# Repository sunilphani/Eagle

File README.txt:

Versioning Note:

version 1.0: First Prototype. PCBs are done and some are soldered.
		1.0b: un-autorouted version

version 1.1: Small improvements to be considered in the next version.
			 PERFORM ALL YOUR CHANGES IN THIS VERSION OR OTHER SUBVERSIONS, NOT IN 1.0 SO AS TO KEEP THE ORIGINAL WAY IT WAS FABRICATED.

			 Changes made in this verision:
			 - added Filter Capacitors at weight sensor amplifier.

		1.1b: un-autorouted verison

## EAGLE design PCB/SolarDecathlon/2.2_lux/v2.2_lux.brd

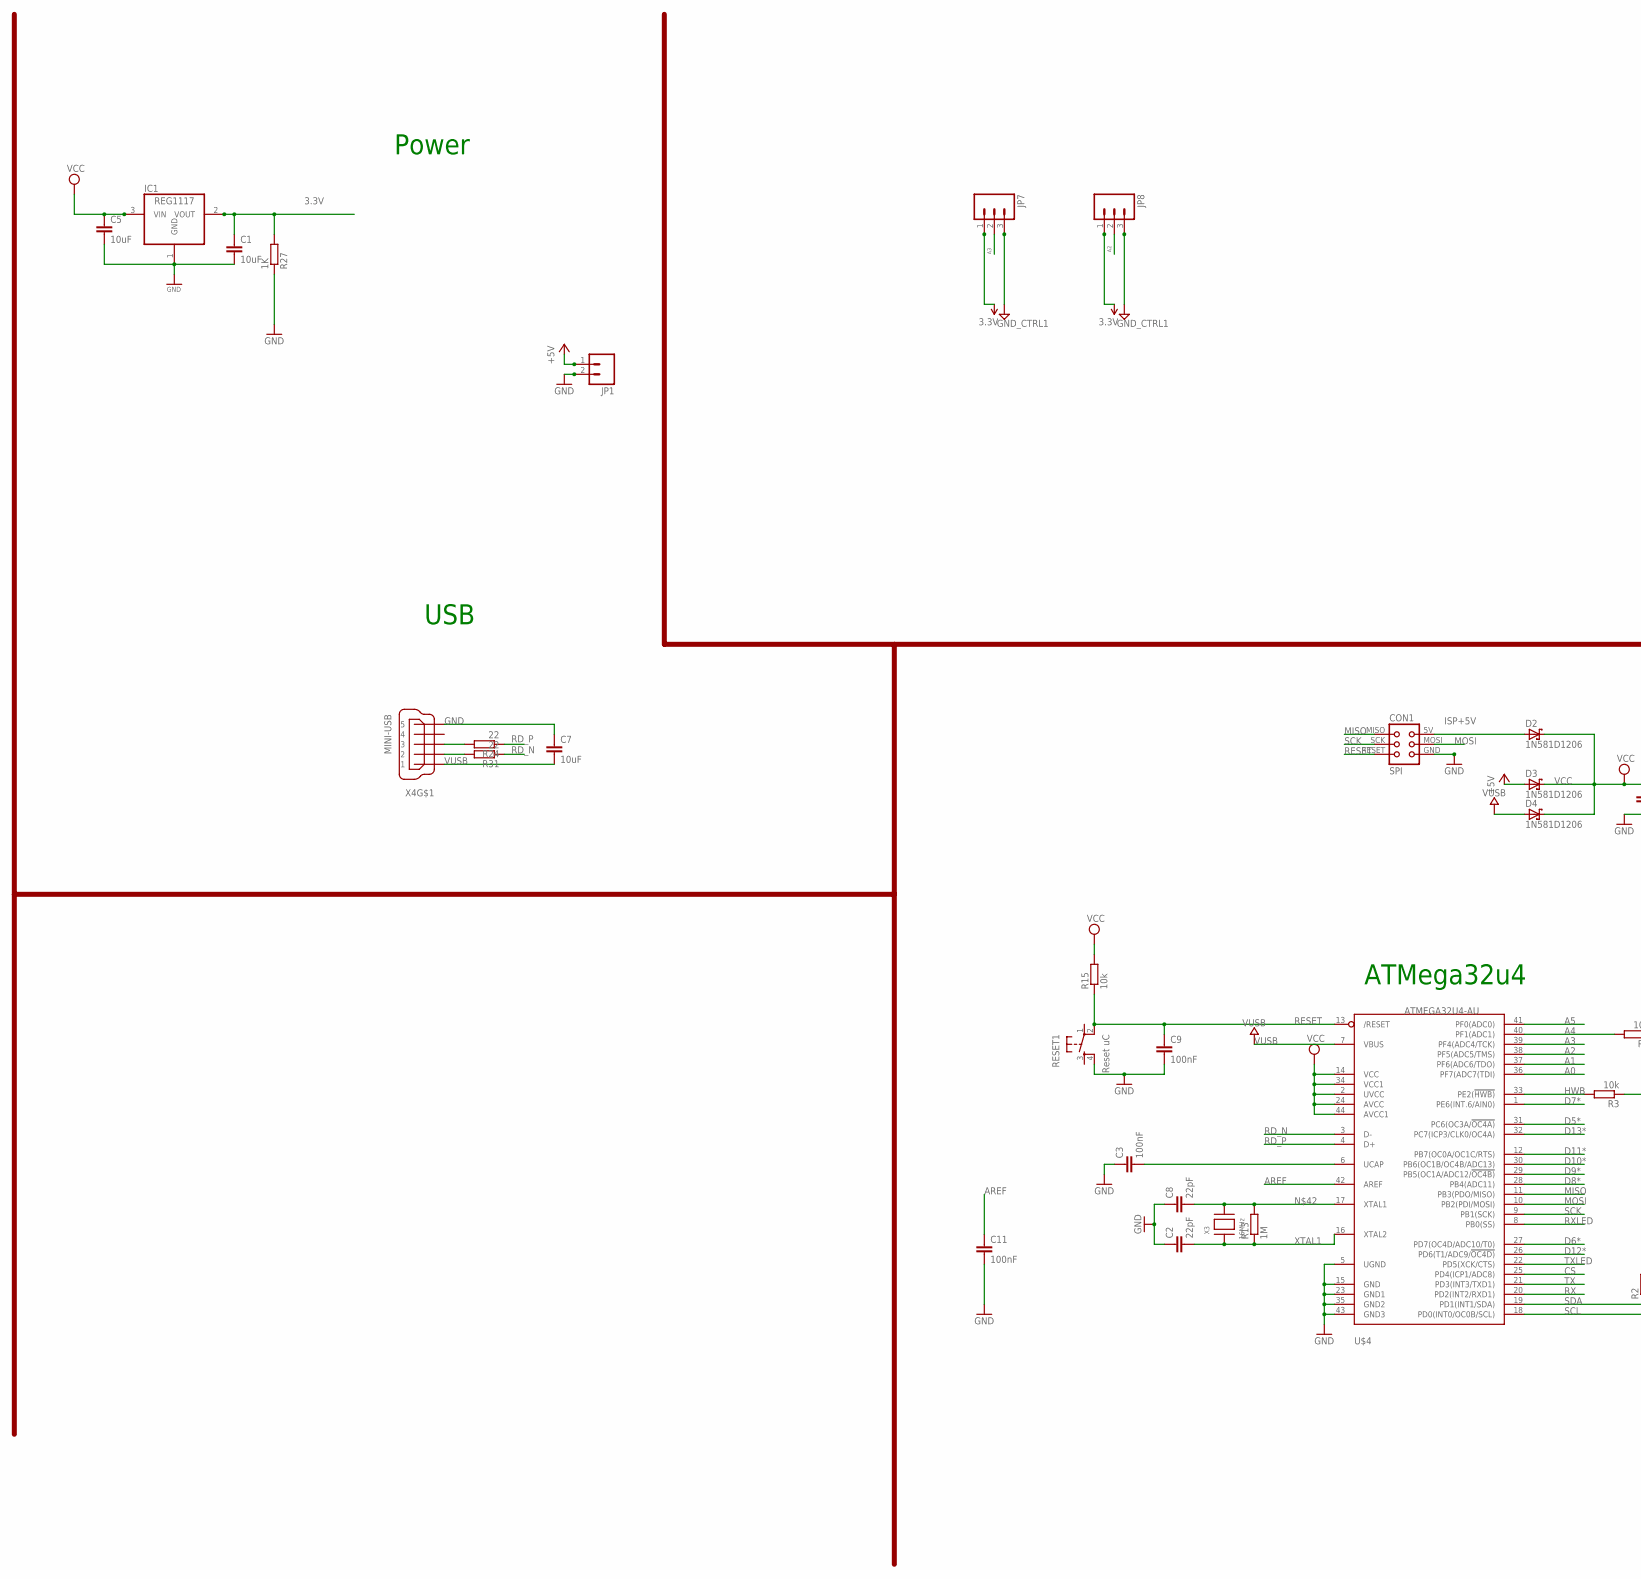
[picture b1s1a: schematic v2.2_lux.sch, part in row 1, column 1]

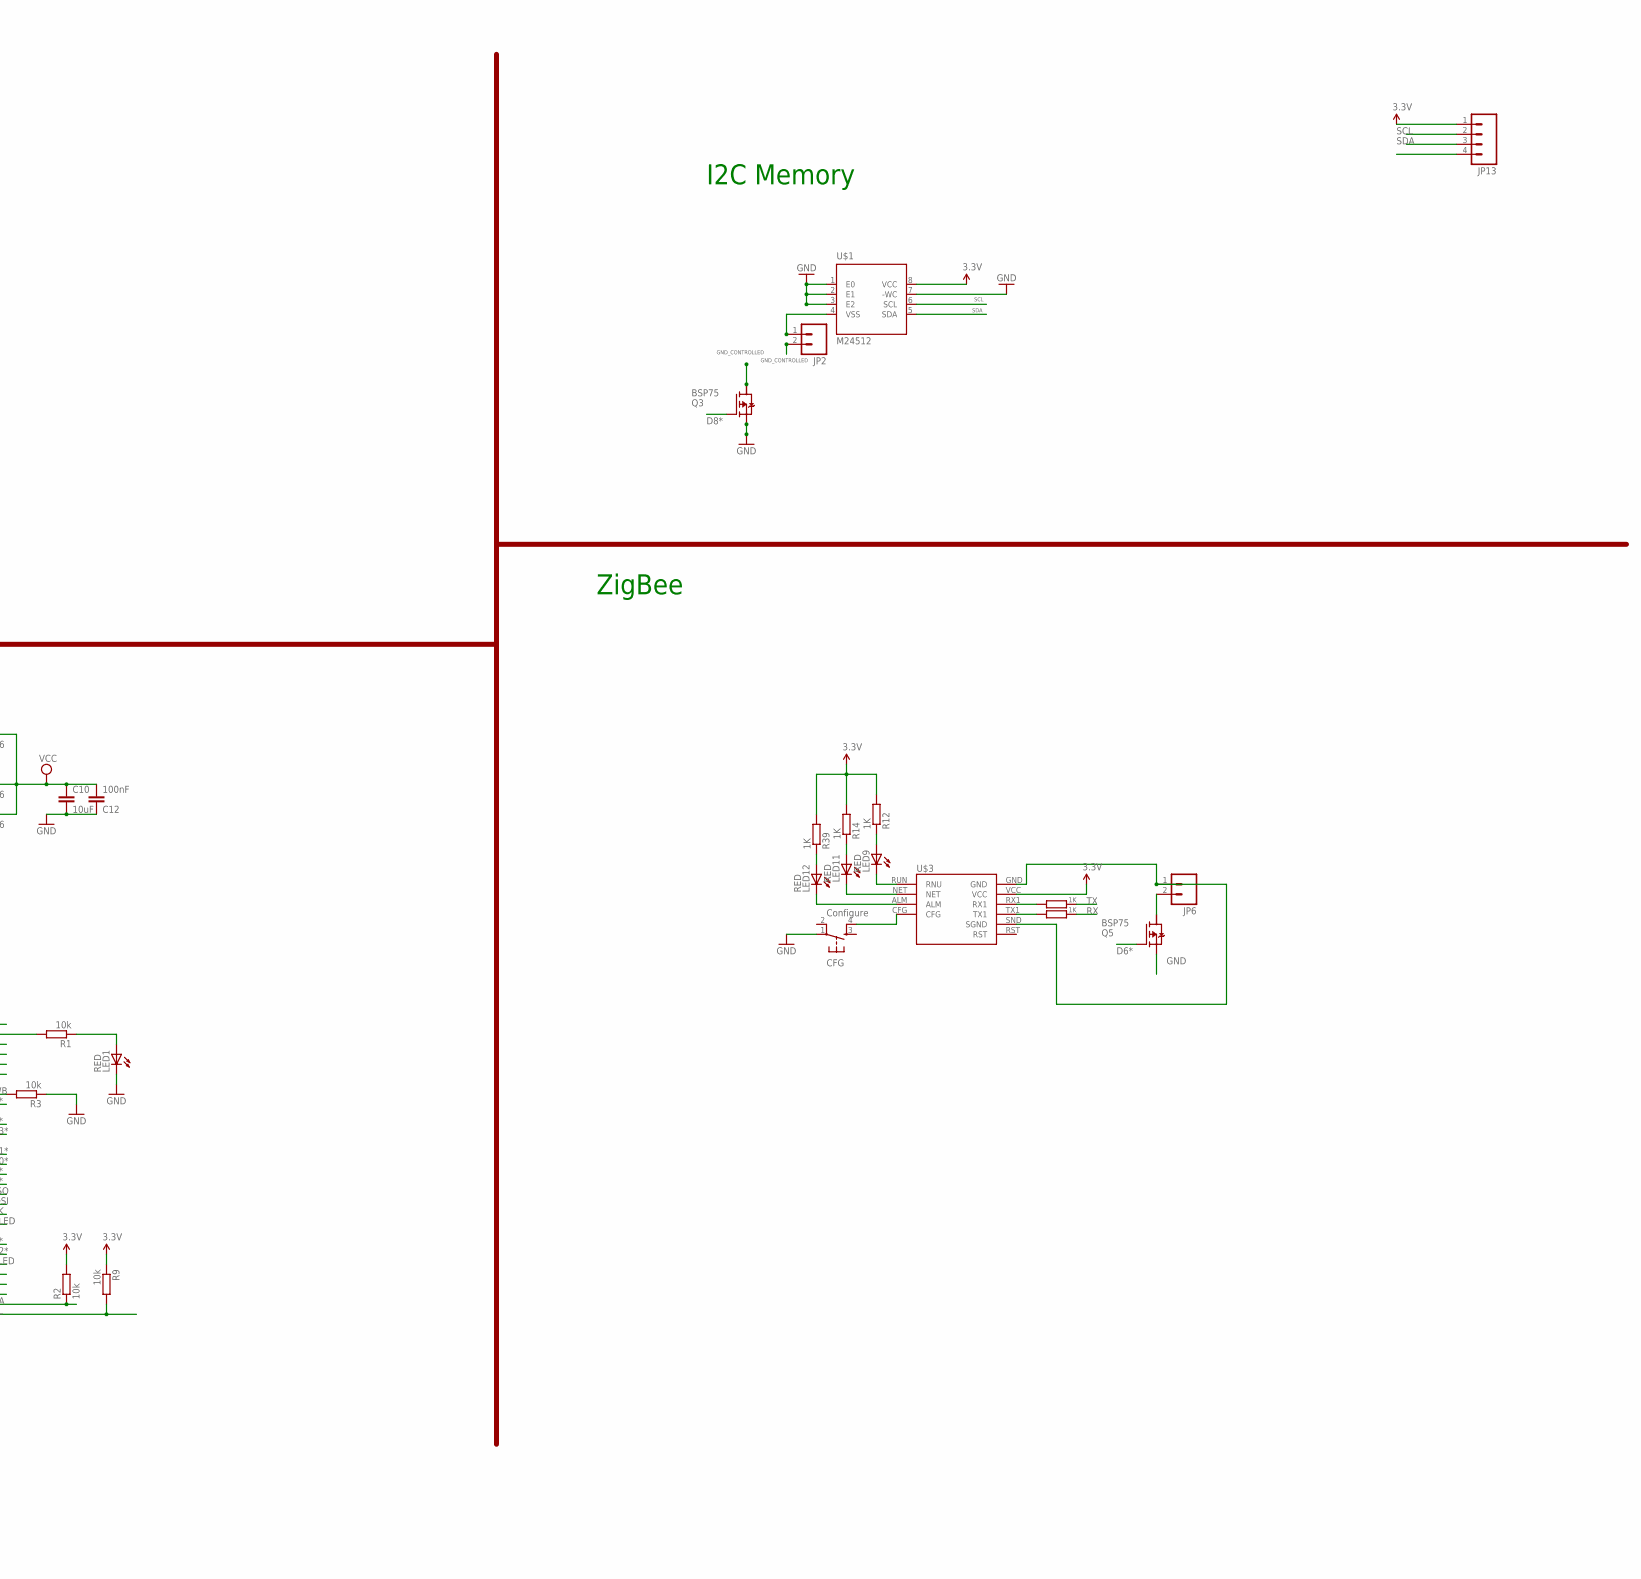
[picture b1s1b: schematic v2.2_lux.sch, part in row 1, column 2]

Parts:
C1, C5, C7, C10: 10uF; C1206
C2, C8: 22pF; C1206
C3, C9, C11, C12: 100nF; C1206
CFG: Configure; TACTILE_SWITCH_SMD
CON1: SPI; TC2030-MCP-NL
D2, D3, D4: 1N581D1206; LED-1206
IC1: REG1117; SOT223
JP1, JP2, JP6: M02LOCK_LONGPADS; 1X02_LOCK_LONGPADS
JP7, JP8: M03LONGPADS; 1X03_LONGPADS
JP13: M04LOCK_LONGPADS; 1X04_LOCK_LONGPADS
LED1, LED9, LED11, LED12: RED; CHIP-LED0805
Q3, Q5: BSP75; PG-SOT-223
R1, R2, R3, R9: 10k; M1206
R8, R11, R12, R14, R27, R39: 1K; R0805
R13: 1M; R1206
R15: 10k; M0805
R24, R31: 22; M1206
RESET1: Reset uC; TACTILE_SWITCH_SMD
U$1: M24512; SO8
U$3: SZ05-ZIGBEETHROUGHHOLE; SZ05-ZIGBEE4
U$4: ATMEGA32U4-AU; TQFP44
X3: 16MHz; NX6035
X4: MINI-USB; 32005-201

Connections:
3.3V: C1.1, IC1.2 (VOUT), JP7.1, JP8.1, JP13.1, R2.2, R9.1, R12.2, R14.2, R27.2, R39.2, U$1.8 (VCC), U$3.VCC
$12: JP2.1, U$1.4 (VSS)
+5V: D3.A, JP1.1
A0: U$4.36 (PF7(ADC7(TDI))
A1: U$4.37 (PF6(ADC6/TDO))
A2: JP8.2, U$4.38 (PF5(ADC5/TMS))
A3: JP7.2, U$4.39 (PF4(ADC4/TCK))
A4: R1.2, U$4.40 (PF1(ADC1))
A5: U$4.41 (PF0(ADC0))
AREF: C11.1, U$4.42 (AREF)
CS: U$4.25 (PD4(ICP1/ADC8))
D5*: U$4.31 (PC6(OC3A/!OC4A))
D6*: Q5.1 (G), U$4.27 (PD7(OC4D/ADC10/T0))
D7*: U$4.1 (PE6(INT.6/AIN0))
D8*: Q3.1 (G), U$4.28 (PB4(ADC11))
D9*: U$4.29 (PB5(OC1A/ADC12/!OC4B))
D10*: U$4.30 (PB6(OC1B/OC4B/ADC13))
D11*: U$4.12 (PB7(OC0A/OC1C/RTS))
D12*: U$4.26 (PD6(T1/ADC9/!OC4D))
D13*: U$4.32 (PC7(ICP3/CLK0/OC4A))
D+USB: R24.2, X4.3
D-USB: R31.2, X4.2
GND: C1.2, C2.1, C3.1, C5.2, C7.1, C8.1, C9.2, C10.2, C11.2, C12.1, CFG.1, CON1.GND, IC1.1 (GND), JP1.2, JP7.3, JP8.3, LED1.C, Q3.3 (S), Q5.3 (S), R3.1, R27.1, RESET1.4, U$1.1 (E0), U$1.2 (E1), U$1.3 (E2), U$1.7 (-WC), U$4.5 (UGND), U$4.15 (GND), U$4.23 (GND1), U$4.35 (GND2), U$4.43 (GND3), X4.5
GND1: LED9.C, U$3.RUN (RNU)
GND2: LED11.C, U$3.NET
GND3: LED12.C, U$3.ALM
GND_CONTROLLED: JP2.2, JP13.4, Q3.2 (D)
HWB: R3.2, U$4.33 (PE2(!HWB))
ISP+5V: CON1.5V (VCC), D2.A
MISO: CON1.MISO, U$4.11 (PB3(PDO/MISO))
MOSI: CON1.MOSI, U$4.10 (PB2(PDI/MOSI))
unnamed: LED1.A, R1.1
unnamed: JP6.2, Q5.2 (D)
unnamed: JP6.1, U$3.GND, U$3.SND (SGND)
unnamed: R11.2, U$3.RX1
unnamed: C3.2, U$4.6 (UCAP)
unnamed: R8.2, U$3.TX1
unnamed: LED9.A, R12.1
unnamed: LED11.A, R14.1
unnamed: LED12.A, R39.1
unnamed: CFG.4, U$3.CFG
unnamed: C8.2, R13.2, U$4.17 (XTAL1), X3.P$2
RD_N: R31.1, U$4.3 (D-)
RD_P: R24.1, U$4.4 (D+)
RESET: C9.1, CON1.RESET, R15.1, RESET1.2, U$4.13 (/RESET)
RX: R8.1, U$4.20 (PD2(INT2/RXD1))
RXLED: U$4.8 (PB0(SS))
SCK: CON1.SCK, U$4.9 (PB1(SCK))
SCL: JP13.2, R9.2, U$1.6 (SCL), U$4.18 (PD0(INT0/OC0B/SCL))
SDA: JP13.3, R2.1, U$1.5 (SDA), U$4.19 (PD1(INT1/SDA))
TX: R11.1, U$4.21 (PD3(INT3/TXD1))
TXLED: U$4.22 (PD5(XCK/CTS))
VCC: C5.1, C10.1, C12.2, D2.C, D3.C, D4.C, IC1.3 (VIN), R15.2, U$4.2 (UVCC), U$4.14 (VCC), U$4.24 (AVCC), U$4.34 (VCC1), U$4.44 (AVCC1)
VUSB: C7.2, D4.A, U$4.7 (VBUS), X4.1
XTAL1: C2.2, R13.1, U$4.16 (XTAL2), X3.P$1

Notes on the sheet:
I2C Memory
ATMega32u4
USB
Power
ZigBee

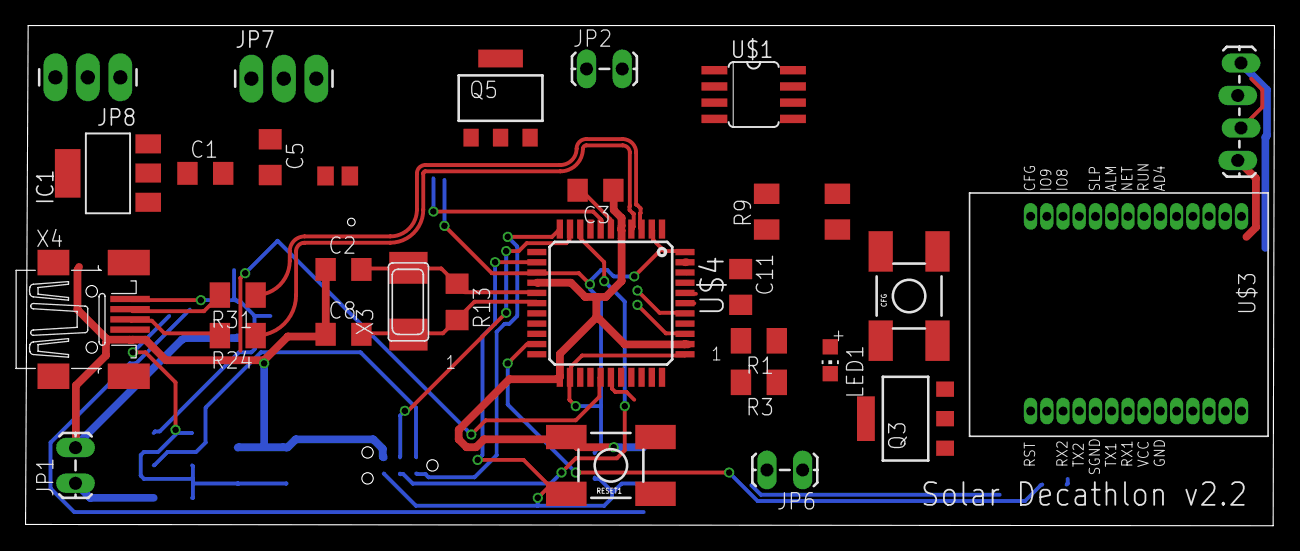
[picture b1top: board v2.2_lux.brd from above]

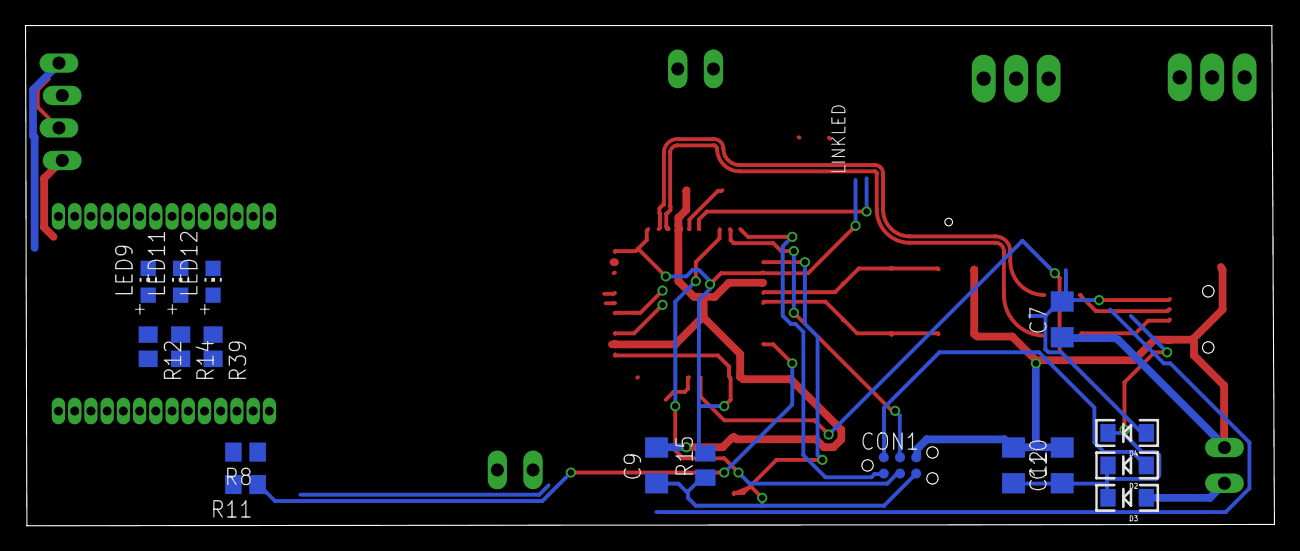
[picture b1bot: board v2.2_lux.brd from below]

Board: 2 copper layers, 97.8 x 39.2 mm, 48 parts (17 on the bottom side), 42 nets.

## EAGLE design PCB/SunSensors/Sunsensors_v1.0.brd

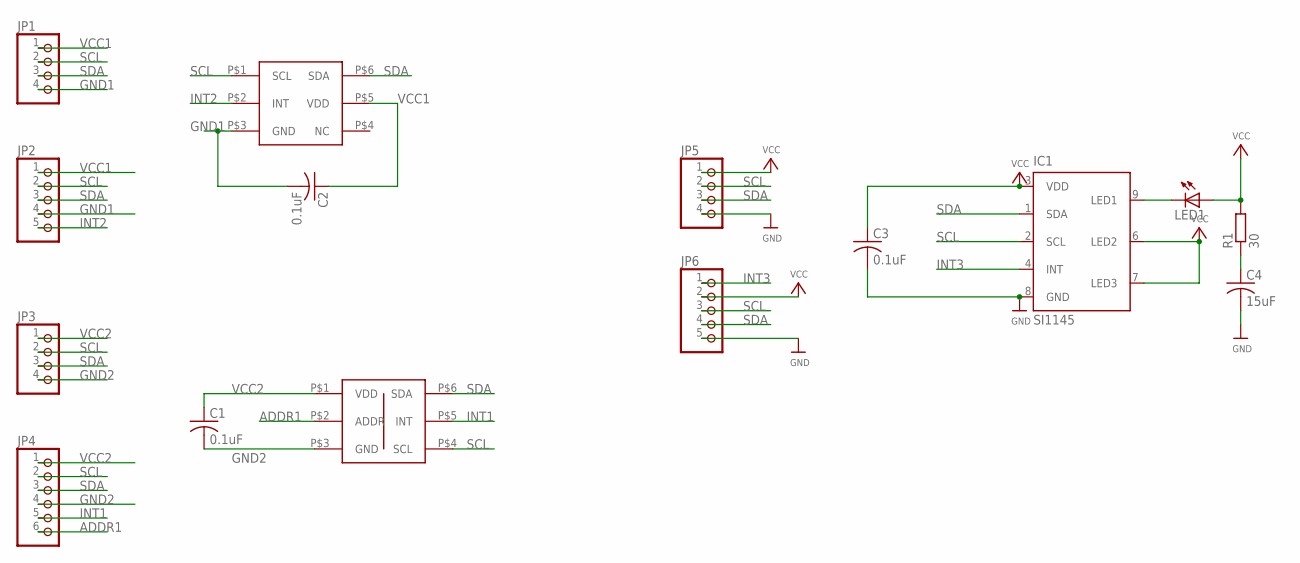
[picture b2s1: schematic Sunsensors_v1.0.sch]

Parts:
C1, C2, C3: 0.1uF; C0805
C4: 15uF; C0805
IC1: SI1145; QFN-10
JP1, JP3, JP5: PINHD-1X4; 1X04
JP2, JP6: PINHD-1X5; 1X05
JP4: PINHD-1X6; 1X06
LED1: LEDCHIPLED_0805; CHIPLED_0805
R1: 30; R1206
U$8: TSL25911FN; ODFN6
U$9: TSL2561T; TMB-6

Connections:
ADDR1: JP4.6, U$9.P$2 (ADDR)
GND: C3.2, C4.2, IC1.8 (GND), JP5.4, JP6.5
GND1: C2.2, JP1.4, JP2.4, U$8.P$3 (GND)
GND2: C1.2, JP3.4, JP4.4, U$9.P$3 (GND)
INT1: JP4.5, U$9.P$5 (INT)
INT2: JP2.5, U$8.P$2 (INT)
INT3: IC1.4 (INT), JP6.1
unnamed: C4.1, R1.1
unnamed: IC1.9 (LED1), LED1.C
SCL: IC1.2 (SCL), JP1.2, JP2.2, JP3.2, JP4.2, JP5.2, JP6.3, U$8.P$1 (SCL), U$9.P$4 (SCL)
SDA: IC1.1 (SDA), JP1.3, JP2.3, JP3.3, JP4.3, JP5.3, JP6.4, U$8.P$6 (SDA), U$9.P$6 (SDA)
VCC: C3.1, IC1.3 (VDD), IC1.6 (LED2), IC1.7 (LED3), JP5.1, JP6.2, LED1.A, R1.2
VCC1: C2.1, JP1.1, JP2.1, U$8.P$5 (VDD)
VCC2: C1.1, JP3.1, JP4.1, U$9.P$1 (VDD)

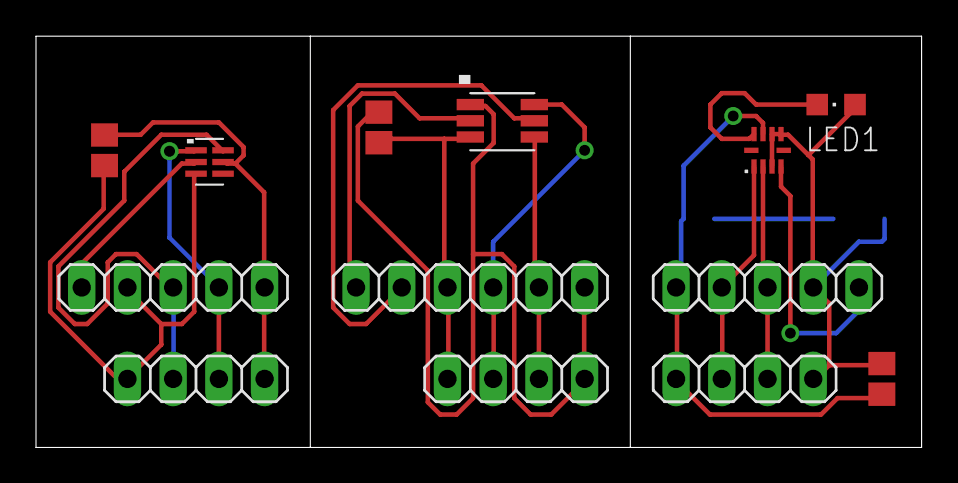
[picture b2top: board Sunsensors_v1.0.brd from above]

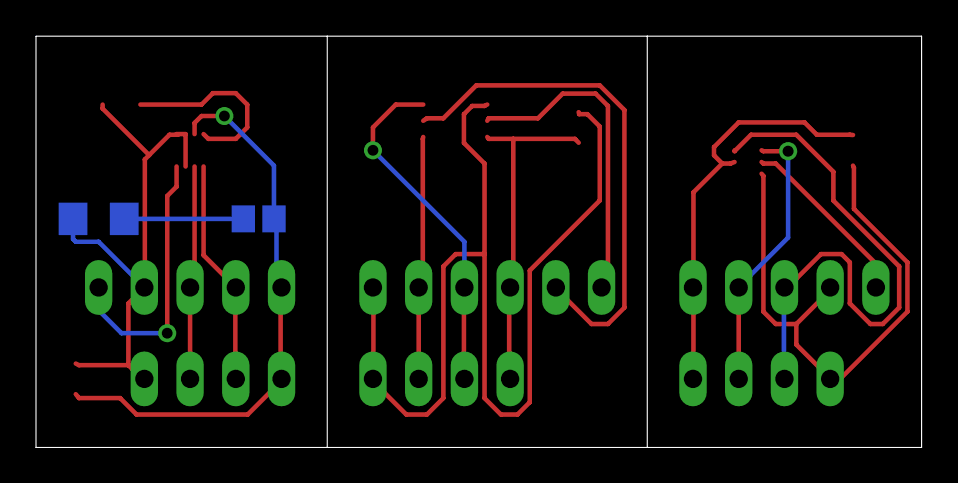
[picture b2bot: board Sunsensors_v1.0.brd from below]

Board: 2 copper layers, 49.2 x 22.9 mm, 15 parts (2 on the bottom side), 14 nets.

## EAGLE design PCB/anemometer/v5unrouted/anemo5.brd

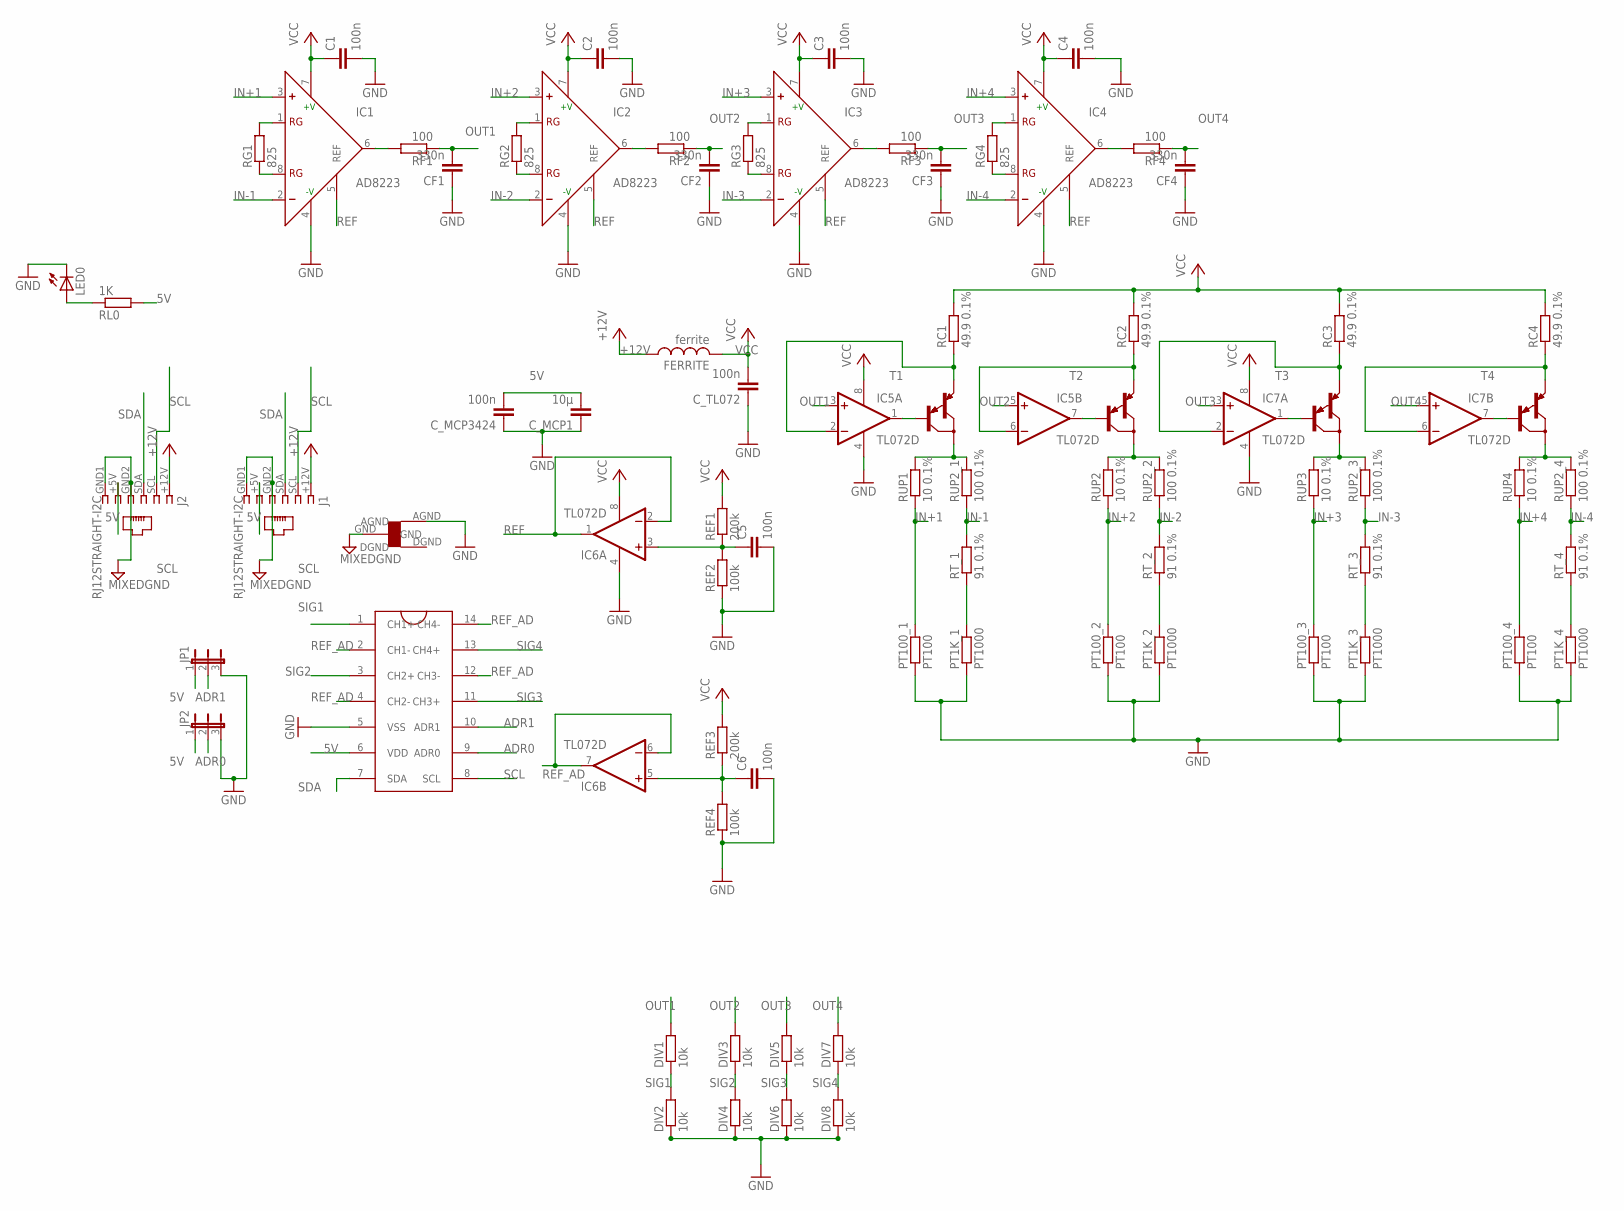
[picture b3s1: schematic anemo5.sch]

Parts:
C1, C2, C3, C4, C5, C6: 100n; C1206
CF1, CF2, CF3, CF4: 330n; C1206
C_MCP1: 10µ; C1206
C_MCP3424: 100n; C1206
C_TL072: 100n; C1206
DIV1, DIV2, DIV3, DIV4, DIV5, DIV6, DIV7, DIV8: 10k; M1206
FERRITE: ferrite; L3216C
IC1, IC2, IC3, IC4: AD8223; SO8
IC5, IC6, IC7: TL072D; SO08
J1, J2: RJ12STRAIGHT-I2C; RJ12-STRAIGHT-I2C
JP1, JP2: JP2E; JP2
LED0: LED1206; LED-1206
PT1K_1, PT1K_2, PT1K_3, PT1K_4: PT1000; M1206
PT100_1, PT100_2, PT100_3, PT100_4: PT100; M1206
RC1, RC2, RC3, RC4: 49.9 0.1%; M1206
REF1, REF3: 200k; M1206
REF2, REF4: 100k; M1206
RF1, RF2, RF3, RF4: 100; M1206
RG1, RG2, RG3, RG4: 825; M1206
RL0: 1K; M1206
RT_1, RT_2, RT_3, RT_4: 91 0.1%; M1206
RUP1, RUP2, RUP3, RUP4: 10 0.1%; M1206
RUP2_1, RUP2_2, RUP2_3, RUP2_4: 100 0.1%; M1206
T1, T2, T3, T4: MMBTA64LT1-PNP_DARL-SOT23-BEC; SOT23-BEC
U$1: MCP3424(SO14); 14LDSOIC
U$2: STARGND; STAR

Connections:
5V: C_MCP1.2, C_MCP3424.2, J1.+5V (5), J2.+5V (5), JP1.1, JP2.1, RL0.2, U$1.6 (VDD)
+12V: FERRITE.1, J1.+12V (1), J2.+12V (1)
ADR0: JP2.2, U$1.9 (ADR0)
ADR1: JP1.2, U$1.10 (ADR1)
GND: C1.2, C2.2, C3.2, C4.2, C5.2, C6.2, CF1.1, CF2.1, CF3.1, CF4.1, C_MCP1.1, C_MCP3424.1, C_TL072.1, DIV2.1, DIV4.1, DIV6.1, DIV8.1, IC1.4 (-V), IC2.4 (-V), IC3.4 (-V), IC4.4 (-V), IC5.4 (V-), IC6.4 (V-), IC7.4 (V-), JP1.3, JP2.3, LED0.C, PT1K_1.1, PT1K_2.1, PT1K_3.1, PT1K_4.1, PT100_1.1, PT100_2.1, PT100_3.1, PT100_4.1, REF2.1, REF4.1, U$1.5 (VSS), U$2.AGND
IN+1: IC1.3 (+), PT100_1.2, RUP1.1
IN+2: IC2.3 (+), PT100_2.2, RUP2.1
IN+3: IC3.3 (+), PT100_3.2, RUP3.1
IN+4: IC4.3 (+), PT100_4.2, RUP4.1
IN-1: IC1.2 (-), RT_1.2, RUP2_1.1
IN-2: IC2.2 (-), RT_2.2, RUP2_2.1
IN-3: IC3.2 (-), RT_3.2, RUP2_3.1
IN-4: IC4.2 (-), RT_4.2, RUP2_4.1
MIXEDGND: J1.GND1 (6), J1.GND2 (4), J2.GND1 (6), J2.GND2 (4), U$2.GND
unnamed: IC1.1 (RG), RG1.2
unnamed: IC1.8 (RG), RG1.1
unnamed: IC2.8 (RG), RG2.1
unnamed: IC2.1 (RG), RG2.2
unnamed: IC3.1 (RG), RG3.2
unnamed: IC3.8 (RG), RG3.1
unnamed: IC4.1 (RG), RG4.2
unnamed: IC4.8 (RG), RG4.1
unnamed: RUP1.2, RUP2_1.2, T1.C
unnamed: C5.1, IC6.3 (+IN), REF1.1, REF2.2
unnamed: RUP2.2, RUP2_2.2, T2.C
unnamed: RUP2_3.2, RUP3.2, T3.C
unnamed: RUP2_4.2, RUP4.2, T4.C
unnamed: LED0.A, RL0.1
unnamed: IC5.2 (-IN), RC1.1, T1.E
unnamed: IC5.6 (-IN), RC2.1, T2.E
unnamed: IC7.2 (-IN), RC3.1, T3.E
unnamed: IC1.6 (OUT), RF1.2
unnamed: IC2.6 (OUT), RF2.2
unnamed: IC3.6 (OUT), RF3.2
unnamed: IC4.6 (OUT), RF4.2
unnamed: IC7.6 (-IN), RC4.1, T4.E
unnamed: PT1K_1.2, RT_1.1
unnamed: C6.1, IC6.5 (+IN), REF3.1, REF4.2
unnamed: PT1K_2.2, RT_2.1
unnamed: PT1K_3.2, RT_3.1
unnamed: PT1K_4.2, RT_4.1
OUT1: CF1.2, DIV1.2, IC5.3 (+IN), RF1.1
OUT1A: IC5.1 (OUT), T1.B
OUT2: CF2.2, DIV3.2, IC5.5 (+IN), RF2.1
OUT2A: IC5.7 (OUT), T2.B
OUT3: CF3.2, DIV5.2, IC7.3 (+IN), RF3.1
OUT3A: IC7.1 (OUT), T3.B
OUT4: CF4.2, DIV7.2, IC7.5 (+IN), RF4.1
OUT4A: IC7.7 (OUT), T4.B
REF: IC1.5 (REF), IC2.5 (REF), IC3.5 (REF), IC4.5 (REF), IC6.1 (OUT), IC6.2 (-IN)
REF_AD: IC6.6 (-IN), IC6.7 (OUT), U$1.2 (CH1-), U$1.4 (CH2-), U$1.12 (CH3-), U$1.14 (CH4-)
SCL: J1.SCL (2), J2.SCL (2), U$1.8 (SCL)
SDA: J1.SDA (3), J2.SDA (3), U$1.7 (SDA)
SIG1: DIV1.1, DIV2.2, U$1.1 (CH1+)
SIG2: DIV3.1, DIV4.2, U$1.3 (CH2+)
SIG3: DIV5.1, DIV6.2, U$1.11 (CH3+)
SIG4: DIV7.1, DIV8.2, U$1.13 (CH4+)
VCC: C1.1, C2.1, C3.1, C4.1, C_TL072.2, FERRITE.2, IC1.7 (+V), IC2.7 (+V), IC3.7 (+V), IC4.7 (+V), IC5.8 (V+), IC6.8 (V+), IC7.8 (V+), RC1.2, RC2.2, RC3.2, RC4.2, REF1.2, REF3.2

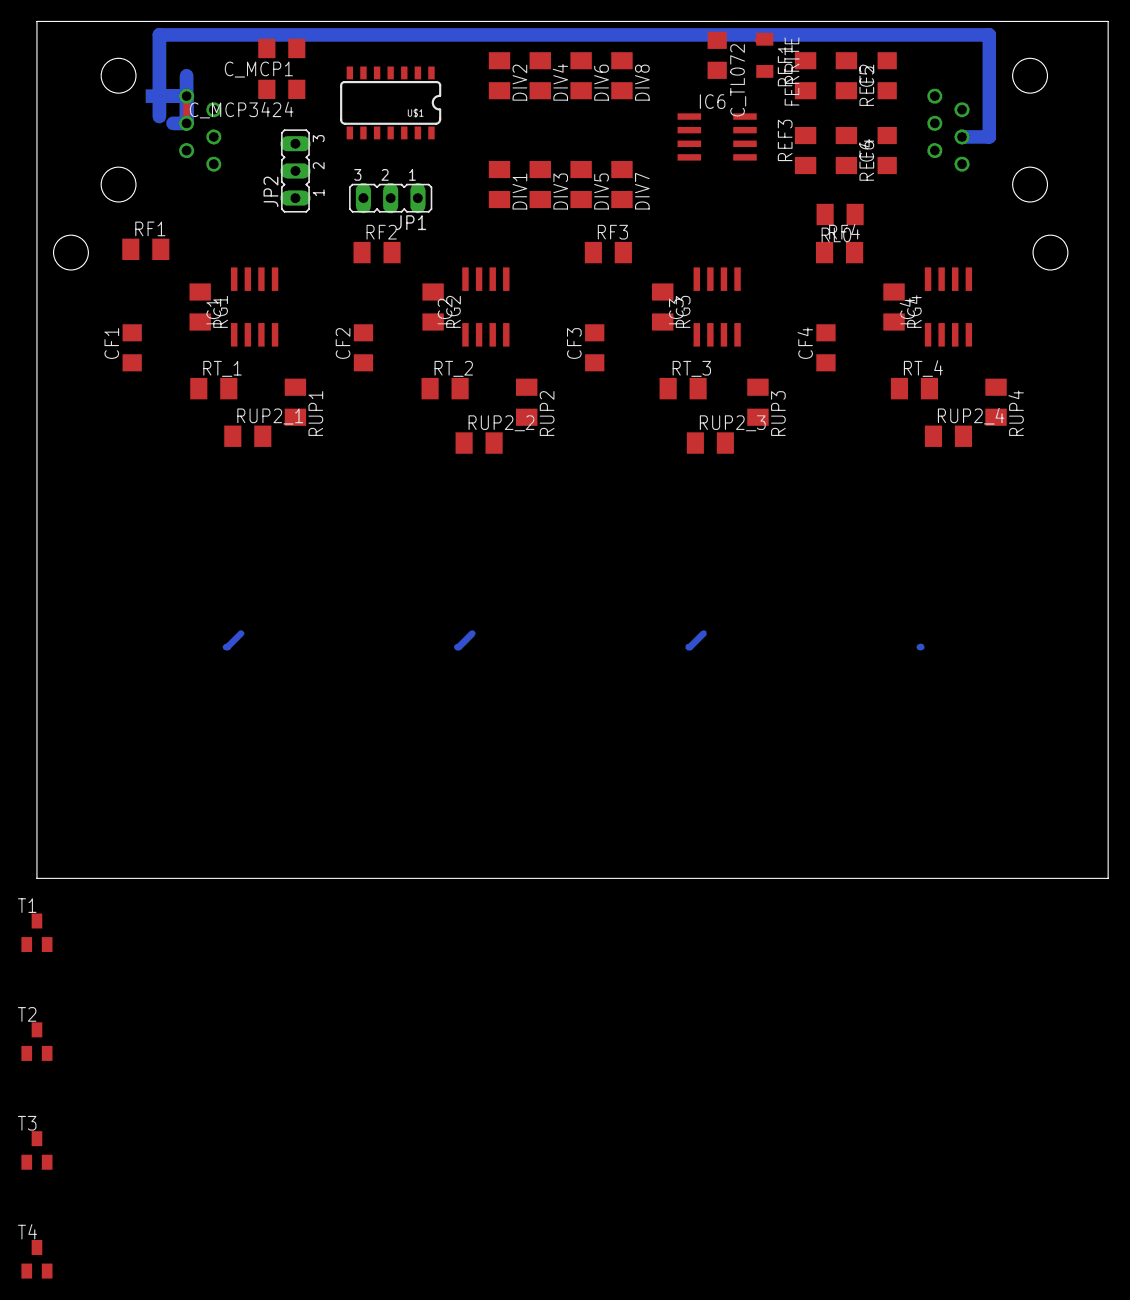
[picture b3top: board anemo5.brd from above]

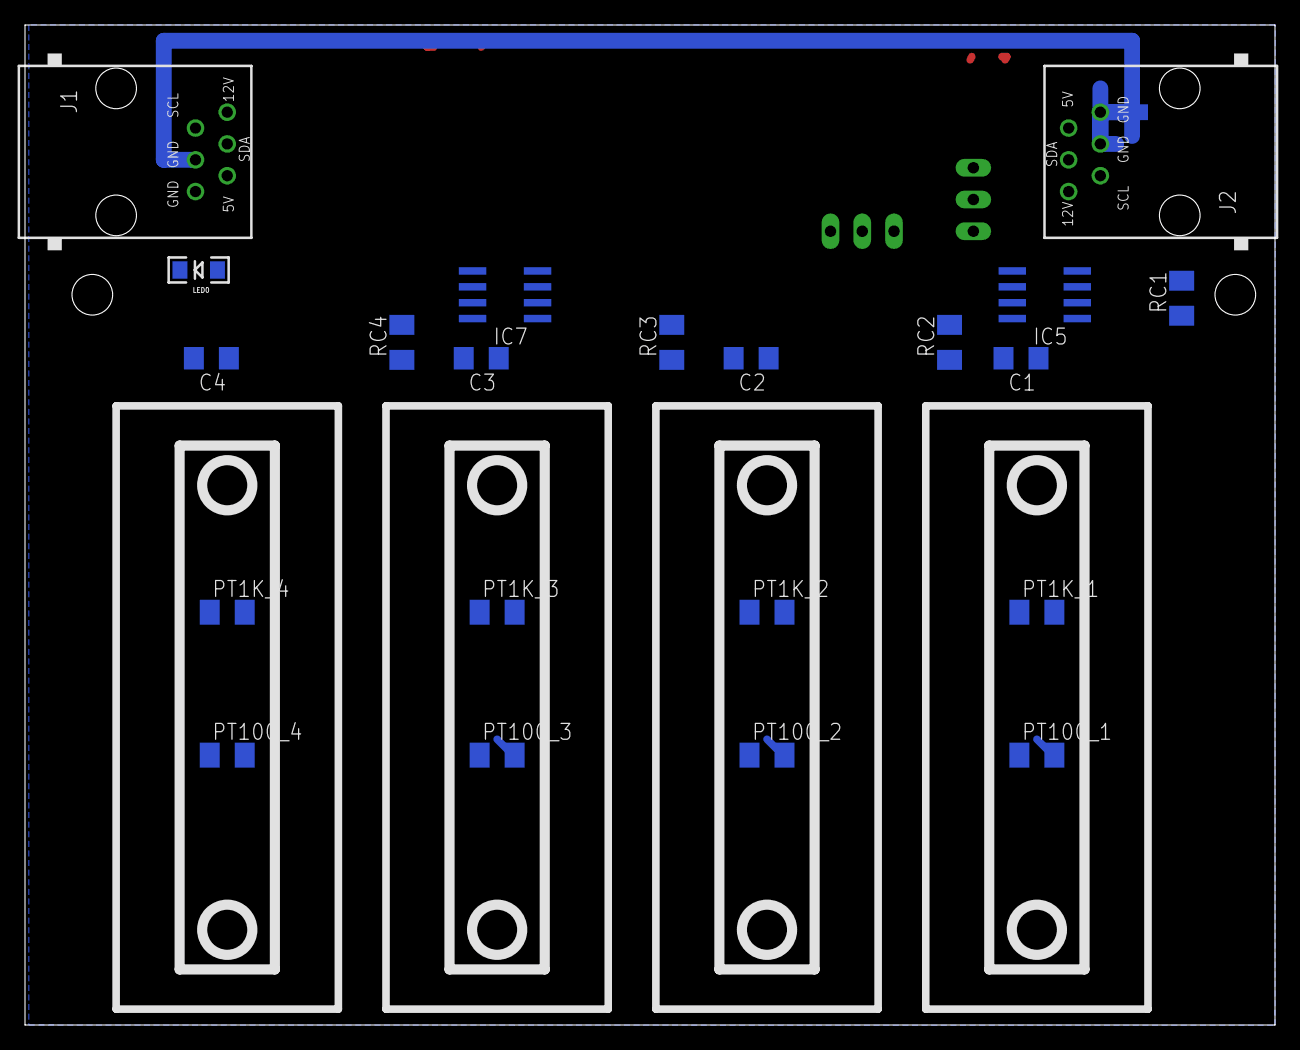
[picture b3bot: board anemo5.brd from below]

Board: 2 copper layers, 100.0 x 80.0 mm, 77 parts (22 on the bottom side), 58 nets.

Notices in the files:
parts and their libraries:
lpatiny: ©2009 ROFA.cz - modified and updated by Robert Darlington ‹rdarlington@gmail.com›
SparkFun: Licensing: CC v3.0 Share-Alike You are welcome to use this library for commercial purposes.
